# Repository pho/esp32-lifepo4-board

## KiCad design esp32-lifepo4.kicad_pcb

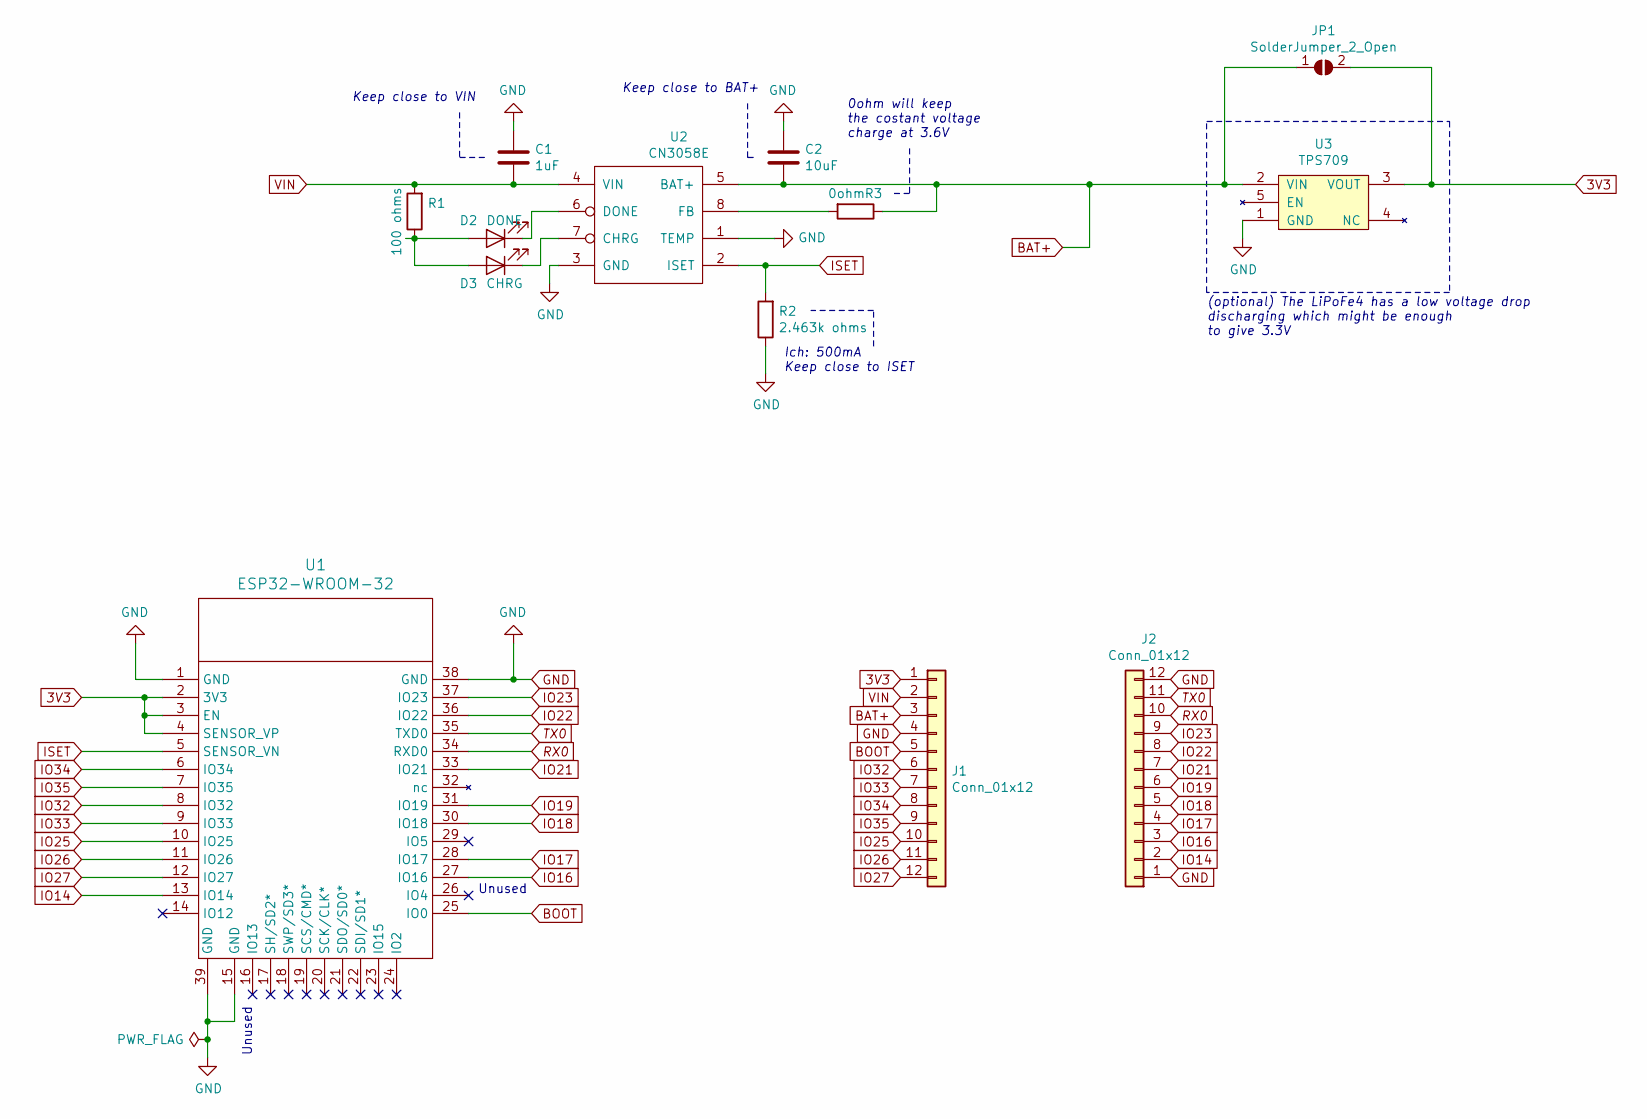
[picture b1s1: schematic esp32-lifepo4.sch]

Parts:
C1: 1uF; C_0805; LCSC C28323
C2: 10uF; C_0805; LCSC C15850
D2: DONE; LED_0603; LCSC C2286
D3: CHRG; LED_0603; LCSC C2286
J1, J2: Conn_01x12; 1X12
JP1: SolderJumper_2_Open; SMT-JUMPER_2_NO_SILK
R1: 100 ohms; 0805; LCSC C17408
R2: 2.463k ohms; 0805; LCSC C17526
R3: 0ohm; 0805; LCSC C17477
U1: ESP32-WROOM-32; ESP32-WROOM-32-Espressif-Symbol-Kicad-62379; LCSC C95209
U2: CN3058E; SOIC-8_3.9x4.9mm_Pitch1.27mm; LCSC C112011
U3: TPS709; SOT-23-5

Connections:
3V3: J1.1, JP1.2 (B), U1.2 (3V3), U1.3 (EN), U1.4 (SENSOR_VP), U3.3 (VOUT)
BAT+: C2.2, J1.3, JP1.1 (A), R3.1, U2.5 (BAT+), U3.2 (VIN)
BOOT: J1.5, U1.25 (IO0)
GND: C1.1, C2.1, J1.4, J2.1, J2.12, R2.1, U1.1 (GND), U1.15 (GND), U1.38 (GND), U1.39 (GND), U2.1 (TEMP), U2.3 (GND), U3.1 (GND)
IO14: J2.2, U1.13 (IO14)
IO16: J2.3, U1.27 (IO16)
IO17: J2.4, U1.28 (IO17)
IO18: J2.5, U1.30 (IO18)
IO19: J2.6, U1.31 (IO19)
IO21: J2.7, U1.33 (IO21)
IO22: J2.8, U1.36 (IO22)
IO23: J2.9, U1.37 (IO23)
IO25: J1.10, U1.10 (IO25)
IO26: J1.11, U1.11 (IO26)
IO27: J1.12, U1.12 (IO27)
IO32: J1.6, U1.8 (IO32)
IO33: J1.7, U1.9 (IO33)
IO34: J1.8, U1.6 (IO34)
IO35: J1.9, U1.7 (IO35)
ISET: R2.2, U1.5 (SENSOR_VN), U2.2 (ISET)
unnamed: D2.1 (K), U2.6 (DONE)
unnamed: D2.2 (A), D3.2 (A), R1.1
unnamed: D3.1 (K), U2.7 (CHRG)
unnamed: R3.2, U2.8 (FB)
RX0: J2.10, U1.34 (RXD0)
TX0: J2.11, U1.35 (TXD0)
VIN: C1.2, J1.2, R1.2, U2.4 (VIN)

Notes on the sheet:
(optional) The LiPoFe4 has a low voltage drop discharging which might be enough to give 3.3V
0ohm will keep the costant voltage charge at 3.6V
Keep close to VIN
Keep close to BAT+
Ich: 500mA Keep close to ISET
Unused

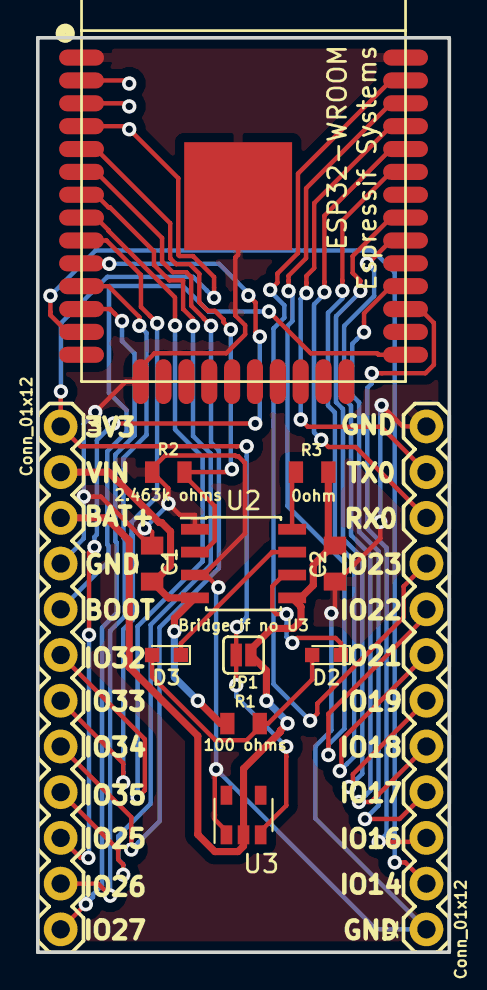
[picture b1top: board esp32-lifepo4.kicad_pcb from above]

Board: 2 copper layers, 22.9 x 50.8 mm, 13 parts (0 on the bottom side), 27 nets.

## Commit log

2019-10-09 added custom lcsc bom plugin
2019-10-20 minor changes
2019-10-20 Slim PCB design
2020-01-06 first test production
2020-01-06 Added symbol and footprint. Removed non-slim version
2020-01-06 Added readme
2020-01-06 remove non-slim gerbers
2020-01-06 re-add the old gerbers
